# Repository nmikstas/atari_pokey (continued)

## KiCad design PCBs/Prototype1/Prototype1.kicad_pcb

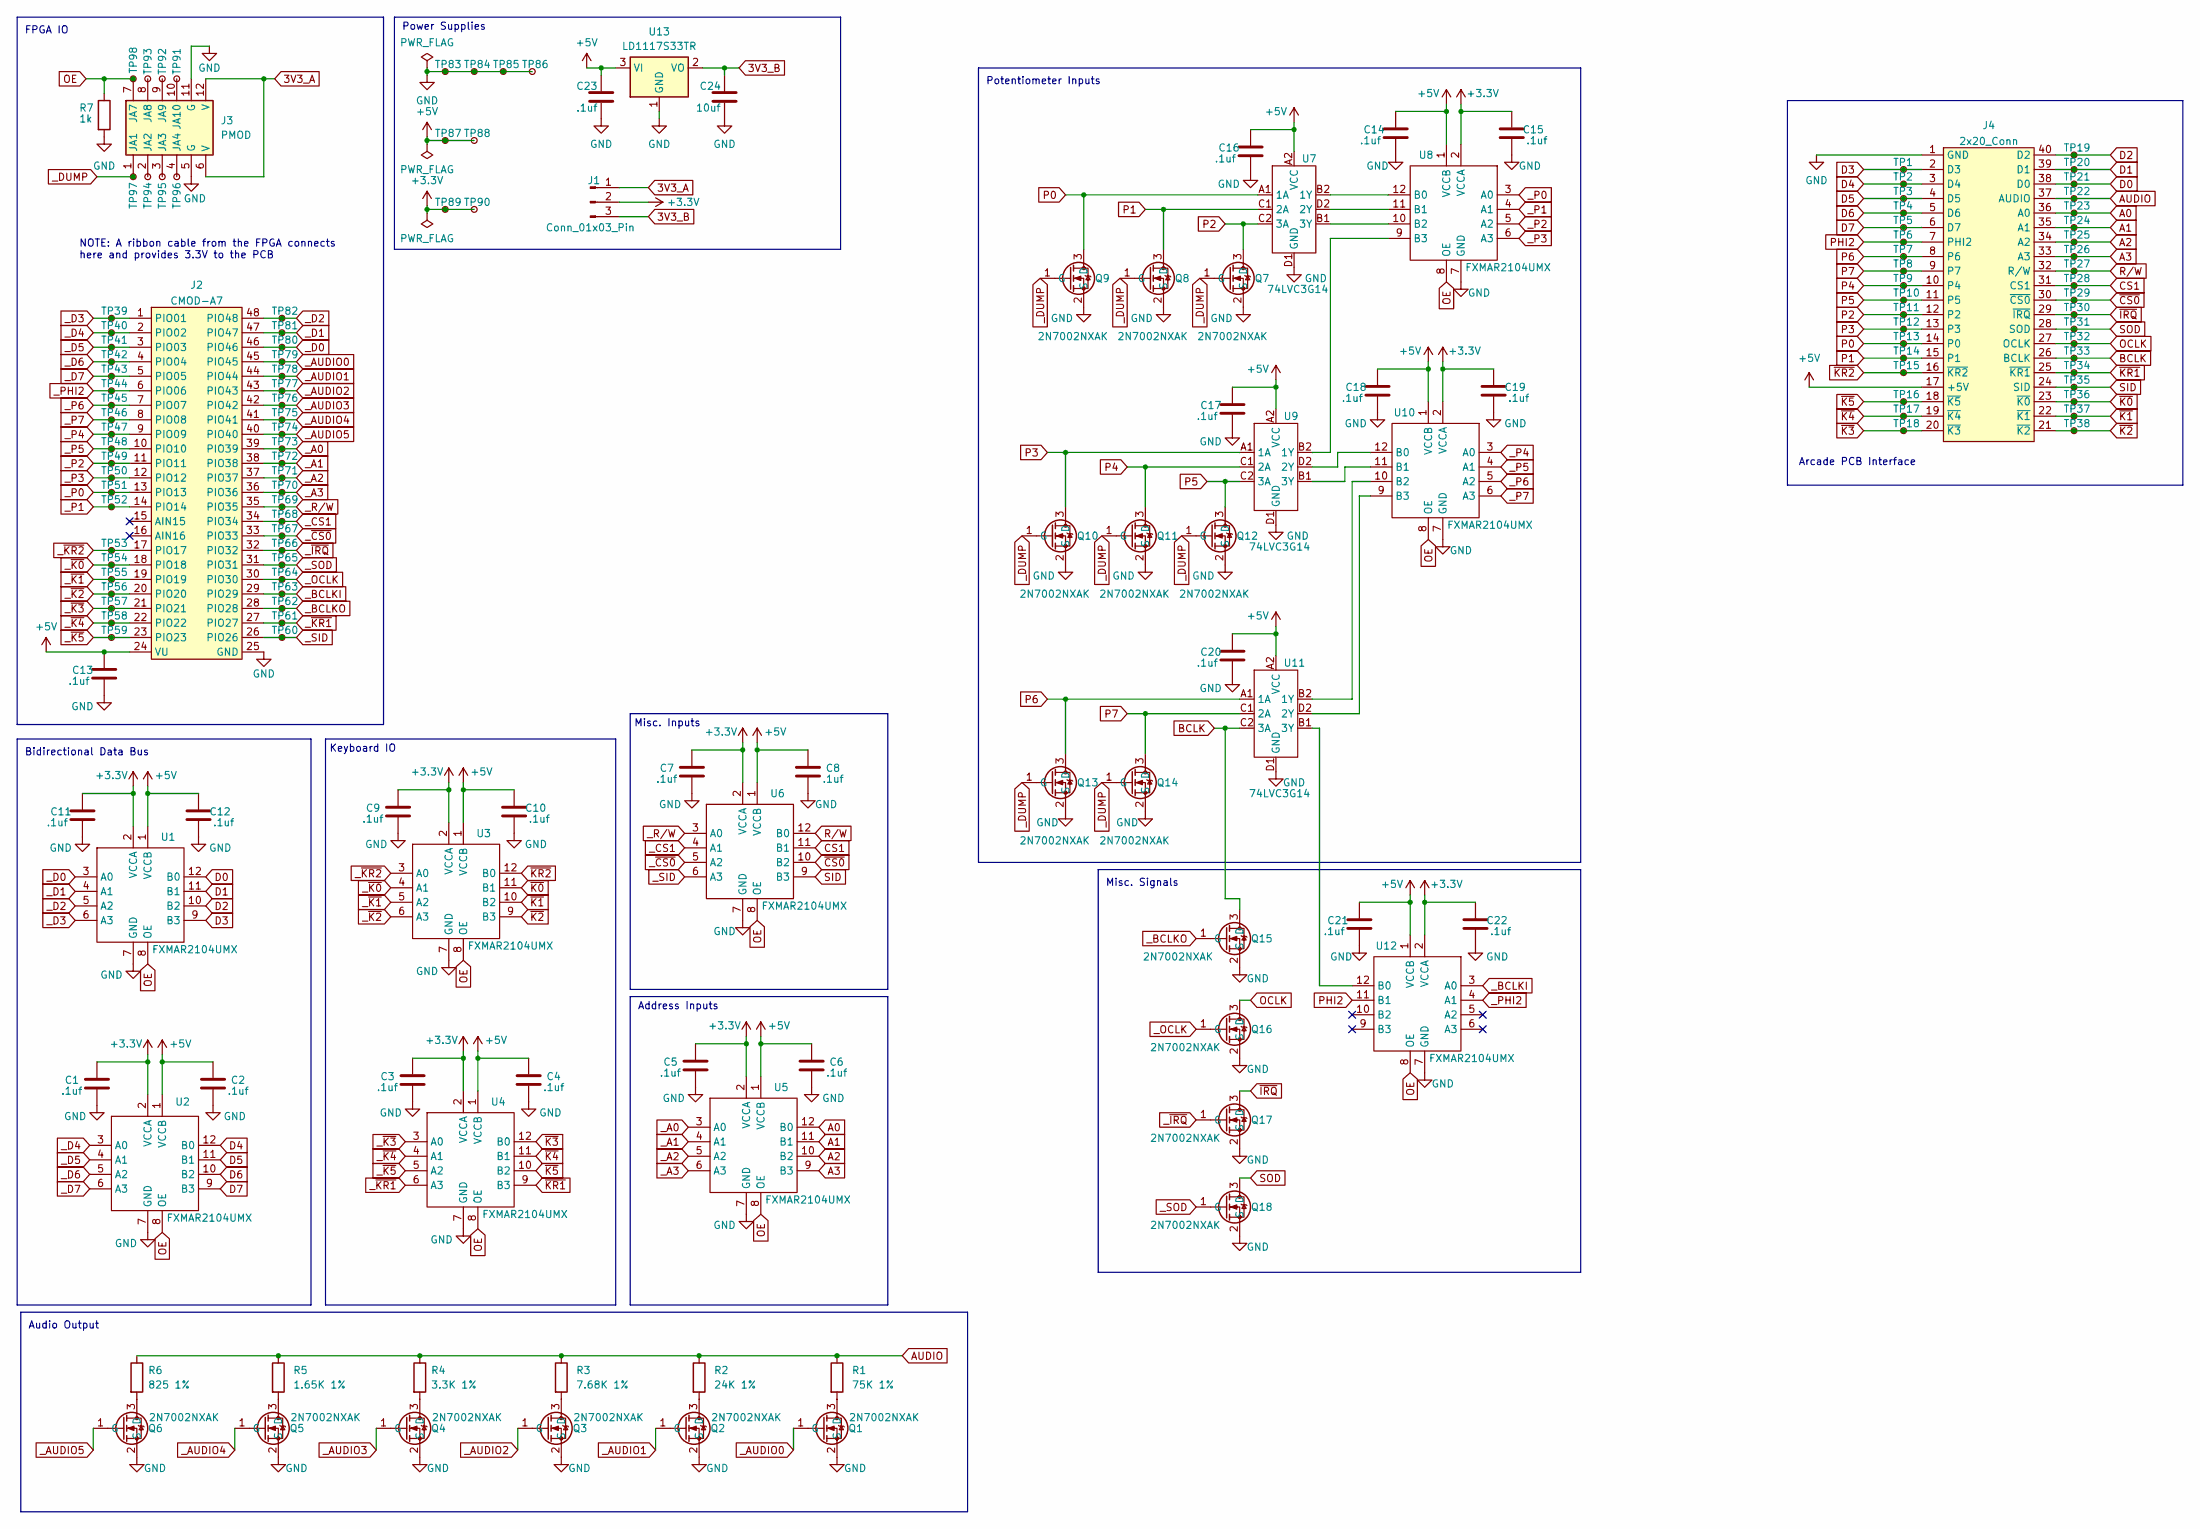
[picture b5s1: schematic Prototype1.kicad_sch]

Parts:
C1, C2, C3, C4, C5, C6, C7, C8, C9, C10, C11, C12, C13, C14, C15, C16, C17, C18, C19, C20, C21, C22, C23: .1uf; C_0402_1005Metric
C24: 10uf; C_0805_2012Metric
J1: Conn_01x03_Pin; PinSocket_1x03_P2.54mm_Vertical
J2: CMOD-A7; Con_2X24
J3: PMOD
J4: 2x20_Conn; Con_2X20
Q1, Q2, Q3, Q4, Q5, Q6, Q7, Q8, Q9, Q10, Q11, Q12, Q13, Q14, Q15, Q16, Q17, Q18: 2N7002NXAK; SOT-23-3
R1: 75K 1%; R_0402_1005Metric
R2: 24K 1%; R_0402_1005Metric
R3: 7.68K 1%; R_0402_1005Metric
R4: 3.3K 1%; R_0402_1005Metric
R5: 1.65K 1%; R_0402_1005Metric
R6: 825 1%; R_0402_1005Metric
R7: 1k; R_0402_1005Metric
TP1, TP2, TP3, TP4, TP5, TP6, TP7, TP8, TP9, TP10, TP11, TP12, TP13, TP14, TP15, TP16, TP17, TP18, TP19, TP20, TP21, TP22, TP23, TP24, TP25, TP26, TP27, TP28, TP29, TP30, TP31, TP32, TP33, TP34, TP35, TP36, TP37, TP38, TP39, TP40, TP41, TP42, TP43, TP44, TP45, TP46, TP47, TP48, TP49, TP50, TP51, TP52, TP53, TP54, TP55, TP56, TP57, TP58, TP59, TP60, TP61, TP62, TP63, TP64, TP65, TP66, TP67, TP68, TP69, TP70, TP71, TP72, TP73, TP74, TP75, TP76, TP77, TP78, TP79, TP80, TP81, TP82, TP83, TP84, TP85, TP86, TP87, TP88, TP89, TP90, TP91, TP92, TP93, TP94, TP95, TP96, TP97, TP98: TP
U1, U2, U3, U4, U5, U6, U8, U10, U12: FXMAR2104UMX; ULTRATHIN_MLP_12L_ONS-L
U7, U9, U11: 74LVC3G14; YZP8
U13: LD1117S33TR; Reg

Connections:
3V3_A: J1.1, J3.6 (V), J3.12 (V)
3V3_B: C24.1, J1.3, U13.2 (VO)
+3.3V: C1.1, C3.1, C5.1, C7.1, C9.1, C11.1, C15.1, C19.1, C22.1, J1.2, TP89.1, TP90.1, U1.2 (VCCA), U2.2 (VCCA), U3.2 (VCCA), U4.2 (VCCA), U5.2 (VCCA), U6.2 (VCCA), U8.2 (VCCA), U10.2 (VCCA), U12.2 (VCCA)
+5V: C2.1, C4.1, C6.1, C8.1, C10.1, C12.1, C13.1, C14.1, C16.1, C17.1, C18.1, C20.1, C21.1, C23.1, J2.24 (VU), J4.17 (+5V), TP87.1, TP88.1, U1.1 (VCCB), U2.1 (VCCB), U3.1 (VCCB), U4.1 (VCCB), U5.1 (VCCB), U6.1 (VCCB), U7.A2 (VCC), U8.1 (VCCB), U9.A2 (VCC), U10.1 (VCCB), U11.A2 (VCC), U12.1 (VCCB), U13.3 (VI)
A0: J4.36 (A0), TP23.1, U5.12 (B0)
A1: J4.35 (A1), TP24.1, U5.11 (B1)
A2: J4.34 (A2), TP25.1, U5.10 (B2)
A3: J4.33 (A3), TP26.1, U5.9 (B3)
AUDIO: J4.37 (AUDIO), R1.1, R2.1, R3.1, R4.1, R5.1, R6.1, TP22.1
BCLK: J4.26 (BCLK), Q15.3 (D), TP33.1, U11.C2 (3A)
CS1: J4.31 (CS1), TP28.1, U6.11 (B1)
D0: J4.38 (D0), TP21.1, U1.12 (B0)
D1: J4.39 (D1), TP20.1, U1.11 (B1)
D2: J4.40 (D2), TP19.1, U1.10 (B2)
D3: J4.2 (D3), TP1.1, U1.9 (B3)
D4: J4.3 (D4), TP2.1, U2.12 (B0)
D5: J4.4 (D5), TP3.1, U2.11 (B1)
D6: J4.5 (D6), TP4.1, U2.10 (B2)
D7: J4.6 (D7), TP5.1, U2.9 (B3)
GND: C1.2, C2.2, C3.2, C4.2, C5.2, C6.2, C7.2, C8.2, C9.2, C10.2, C11.2, C12.2, C13.2, C14.2, C15.2, C16.2, C17.2, C18.2, C19.2, C20.2, C21.2, C22.2, C23.2, C24.2, J2.25 (GND), J3.5 (G), J3.11 (G), J4.1 (GND), Q1.2 (S), Q2.2 (S), Q3.2 (S), Q4.2 (S), Q5.2 (S), Q6.2 (S), Q7.2 (S), Q8.2 (S), Q9.2 (S), Q10.2 (S), Q11.2 (S), Q12.2 (S), Q13.2 (S), Q14.2 (S), Q15.2 (S), Q16.2 (S), Q17.2 (S), Q18.2 (S), R7.2, TP83.1, TP84.1, TP85.1, TP86.1, U1.7 (GND), U2.7 (GND), U3.7 (GND), U4.7 (GND), U5.7 (GND), U6.7 (GND), U7.D1 (GND), U8.7 (GND), U9.D1 (GND), U10.7 (GND), U11.D1 (GND), U12.7 (GND), U13.1 (GND)
unnamed: J3.2 (JA2), TP94.1
unnamed: J3.3 (JA3), TP95.1
unnamed: J3.4 (JA4), TP96.1
unnamed: J3.8 (JA8), TP93.1
unnamed: J3.9 (JA9), TP92.1
unnamed: J3.10 (JA10), TP91.1
unnamed: Q1.3 (D), R1.2
unnamed: Q2.3 (D), R2.2
unnamed: Q3.3 (D), R3.2
unnamed: Q4.3 (D), R4.2
unnamed: Q5.3 (D), R5.2
unnamed: Q6.3 (D), R6.2
unnamed: U7.B2 (1Y), U8.12 (B0)
unnamed: U7.D2 (2Y), U8.11 (B1)
unnamed: U7.B1 (3Y), U8.10 (B2)
unnamed: U8.9 (B3), U9.B2 (1Y)
unnamed: U9.D2 (2Y), U10.12 (B0)
unnamed: U9.B1 (3Y), U10.11 (B1)
unnamed: U10.10 (B2), U11.B2 (1Y)
unnamed: U10.9 (B3), U11.D2 (2Y)
unnamed: U11.B1 (3Y), U12.12 (B0)
OCLK: J4.27 (OCLK), Q16.3 (D), TP32.1
OE: J3.7 (JA7), R7.1, TP98.1, U1.8 (OE), U2.8 (OE), U3.8 (OE), U4.8 (OE), U5.8 (OE), U6.8 (OE), U8.8 (OE), U10.8 (OE), U12.8 (OE)
P0: J4.14 (P0), Q9.3 (D), TP13.1, U7.A1 (1A)
P1: J4.15 (P1), Q8.3 (D), TP14.1, U7.C1 (2A)
P2: J4.12 (P2), Q7.3 (D), TP11.1, U7.C2 (3A)
P3: J4.13 (P3), Q10.3 (D), TP12.1, U9.A1 (1A)
P4: J4.10 (P4), Q11.3 (D), TP9.1, U9.C1 (2A)
P5: J4.11 (P5), Q12.3 (D), TP10.1, U9.C2 (3A)
P6: J4.8 (P6), Q13.3 (D), TP7.1, U11.A1 (1A)
P7: J4.9 (P7), Q14.3 (D), TP8.1, U11.C1 (2A)
PHI2: J4.7 (PHI2), TP6.1, U12.11 (B1)
R/W: J4.32 (R/W), TP27.1, U6.12 (B0)
SID: J4.24 (SID), TP35.1, U6.9 (B3)
SOD: J4.28 (SOD), Q18.3 (D), TP31.1
_A0: J2.39 (PIO39), TP73.1, U5.3 (A0)
_A1: J2.38 (PIO38), TP72.1, U5.4 (A1)
_A2: J2.37 (PIO37), TP71.1, U5.5 (A2)
_A3: J2.36 (PIO36), TP70.1, U5.6 (A3)
_AUDIO0: J2.45 (PIO45), Q1.1 (G), TP79.1
_AUDIO1: J2.44 (PIO44), Q2.1 (G), TP78.1
_AUDIO2: J2.43 (PIO43), Q3.1 (G), TP77.1
_AUDIO3: J2.42 (PIO42), Q4.1 (G), TP76.1
_AUDIO4: J2.41 (PIO41), Q5.1 (G), TP75.1
_AUDIO5: J2.40 (PIO40), Q6.1 (G), TP74.1
_BCLKI: J2.29 (PIO29), TP63.1, U12.3 (A0)
_BCLKO: J2.28 (PIO28), Q15.1 (G), TP62.1
_CS1: J2.34 (PIO34), TP68.1, U6.4 (A1)
_D0: J2.46 (PIO46), TP80.1, U1.3 (A0)
_D1: J2.47 (PIO47), TP81.1, U1.4 (A1)
_D2: J2.48 (PIO48), TP82.1, U1.5 (A2)
_D3: J2.1 (PIO01), TP39.1, U1.6 (A3)
_D4: J2.2 (PIO02), TP40.1, U2.3 (A0)
_D5: J2.3 (PIO03), TP41.1, U2.4 (A1)
_D6: J2.4 (PIO04), TP42.1, U2.5 (A2)
_D7: J2.5 (PIO05), TP43.1, U2.6 (A3)
_DUMP: J3.1 (JA1), Q7.1 (G), Q8.1 (G), Q9.1 (G), Q10.1 (G), Q11.1 (G), Q12.1 (G), Q13.1 (G), Q14.1 (G), TP97.1
_OCLK: J2.30 (PIO30), Q16.1 (G), TP64.1
_P0: J2.13 (PIO13), TP51.1, U8.3 (A0)
_P1: J2.14 (PIO14), TP52.1, U8.4 (A1)
_P2: J2.11 (PIO11), TP49.1, U8.5 (A2)
_P3: J2.12 (PIO12), TP50.1, U8.6 (A3)
_P4: J2.9 (PIO09), TP47.1, U10.3 (A0)
_P5: J2.10 (PIO10), TP48.1, U10.4 (A1)
_P6: J2.7 (PIO07), TP45.1, U10.5 (A2)
_P7: J2.8 (PIO08), TP46.1, U10.6 (A3)
_PHI2: J2.6 (PIO06), TP44.1, U12.4 (A1)
_R/W: J2.35 (PIO35), TP69.1, U6.3 (A0)
_SID: J2.26 (PIO26), TP60.1, U6.6 (A3)
_SOD: J2.31 (PIO31), Q18.1 (G), TP65.1
_~CS0: J2.33 (PIO33), TP67.1, U6.5 (A2)
_~IRQ: J2.32 (PIO32), Q17.1 (G), TP66.1
_~K0: J2.18 (PIO18), TP54.1, U3.4 (A1)
_~K1: J2.19 (PIO19), TP55.1, U3.5 (A2)
_~K2: J2.20 (PIO20), TP56.1, U3.6 (A3)
_~K3: J2.21 (PIO21), TP57.1, U4.3 (A0)
_~K4: J2.22 (PIO22), TP58.1, U4.4 (A1)
_~K5: J2.23 (PIO23), TP59.1, U4.5 (A2)
_~KR1: J2.27 (PIO27), TP61.1, U4.6 (A3)
_~KR2: J2.17 (PIO17), TP53.1, U3.3 (A0)
~CS0: J4.30 (~CS0), TP29.1, U6.10 (B2)
~IRQ: J4.29 (~IRQ), Q17.3 (D), TP30.1
~K0: J4.23 (~K0), TP36.1, U3.11 (B1)
~K1: J4.22 (~K1), TP37.1, U3.10 (B2)
~K2: J4.21 (~K2), TP38.1, U3.9 (B3)
~K3: J4.20 (~K3), TP18.1, U4.12 (B0)
~K4: J4.19 (~K4), TP17.1, U4.11 (B1)
~K5: J4.18 (~K5), TP16.1, U4.10 (B2)
~KR1: J4.25 (~KR1), TP34.1, U4.9 (B3)
~KR2: J4.16 (~KR2), TP15.1, U3.12 (B0)

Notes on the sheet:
Arcade PCB Interface
Bidirectional Data Bus
Address Inputs
Misc. Signals
Potentiometer Inputs
Misc. Inputs
Keyboard IO
FPGA IO
NOTE: A ribbon cable from the FPGA connects here and provides 3.3V to the PCB
Audio Output
Power Supplies

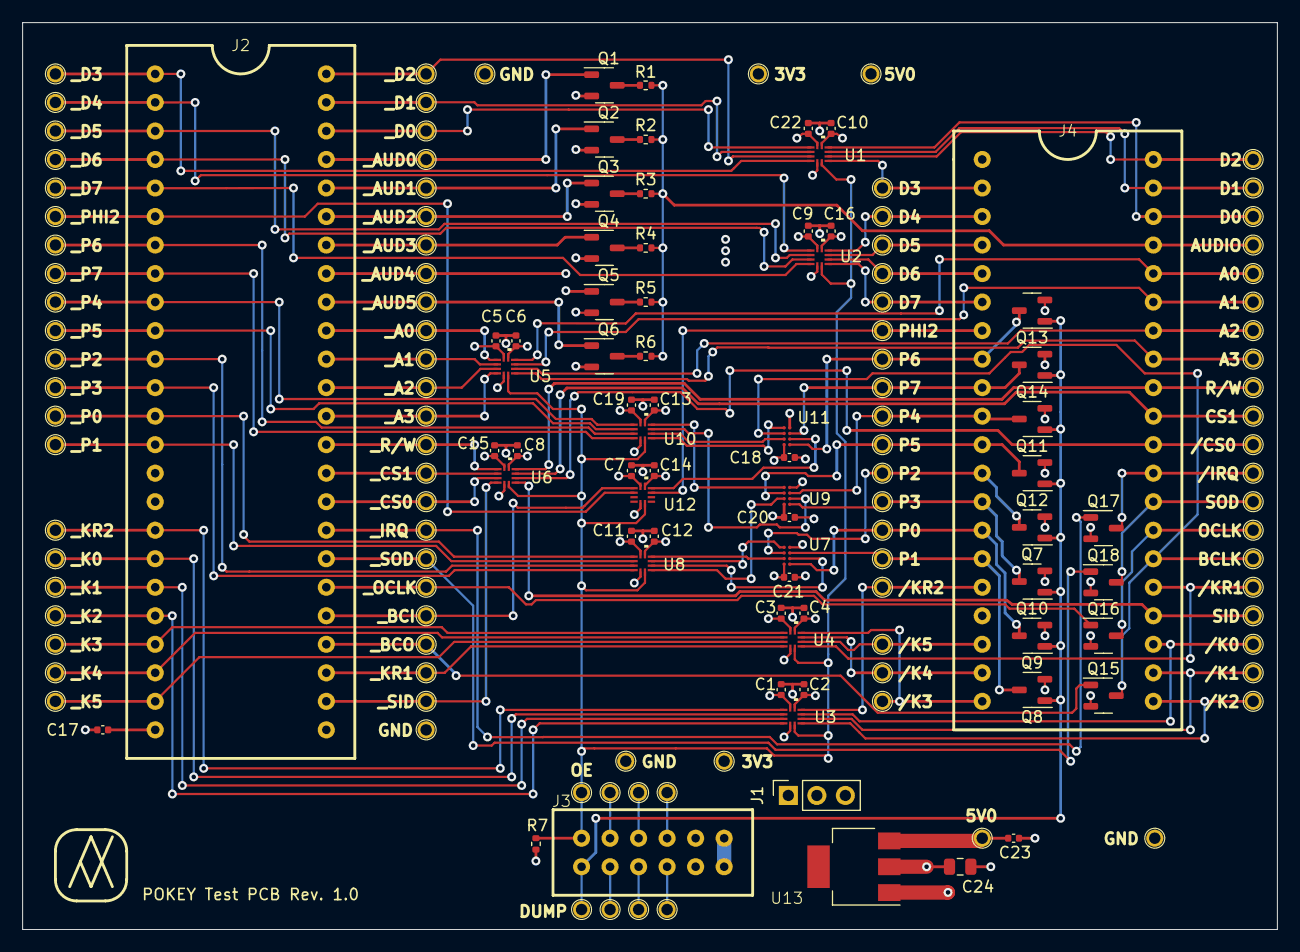
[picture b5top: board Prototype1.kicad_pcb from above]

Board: 4 copper layers, 111.8 x 80.8 mm, 164 parts (0 on the bottom side), 110 nets.

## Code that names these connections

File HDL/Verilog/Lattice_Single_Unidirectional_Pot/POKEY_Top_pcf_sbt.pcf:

# ##############################################################################

# iCEcube PCF

# Version:            2020.12.27943

# File Generated:     Dec 5 2024 22:41:23

# Family & Device:    iCE40HX8K

# Package:            CB132

# ##############################################################################

###IOSet List 53
set_io d[7] K4
set_io irq C7
set_io k[1] H12
set_io leds[3] K14
set_io bclko C11
set_io p[2] A7
set_io d[1] K3
set_io en F4
set_io audio[5] D1
set_io k[4] H11
set_io leds[4] L12
set_io p[4] D5
set_io d[3] J1
set_io dev_clk P7
set_io k[2] J12
set_io leds[6] M12
set_io p[6] C4
set_io a[1] H4
set_io audio[2] G3
set_io d[5] J3
set_io k[3] G11
set_io kr[1] D14
set_io leds[1] K11
set_io p[1] A12
set_io sod D6
set_io a[2] F3
set_io audio[1] H3
set_io bclki B14
set_io d[4] M1
set_io k[0] C14
set_io kr[2] D12
set_io leds[0] J11
set_io oclk D7
set_io p[0] C12
set_io rw C1
set_io sid A2
set_io a[3] B1
set_io audio[0] G1
set_io p[3] C6
set_io d[6] L1
set_io leds[2] K12
set_io dump A11
set_io leds[5] L14
set_io p[5] A10
set_io d[0] P1
set_io audio[4] E1
set_io clk A6
set_io k[5] D11
set_io leds[7] N14
set_io p[7] A1
set_io a[0] G4
set_io audio[3] H1
set_io d[2] N1

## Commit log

2022-12-24 Added some images
2022-12-25 Finished clock gen core and restructured project folders
2023-01-03 Worked on frequency control registers and simulations
2023-01-04 Completed frequency controller simulations and added poly core images
2023-01-05 Performed fequency control register simulations
2023-01-07 Worked on poly core simulations
2023-01-07 Added MAME random number sequences in a text file
2023-01-07 Added rng image
2023-01-07 Changed init signal on the 4-bit poly so it is asynchronous
2023-01-08 Updated poly_core
2023-01-13 Finished the IO core
2023-01-13 Rearranged the structure of the repository
2023-01-14 Added documents for the POT core
2023-01-14 Created simulation for POT core counter
2023-01-16 Finished the POT core code and simulations
2023-01-17 Added pot core simulation images
2023-01-21 Made images for 2 registers and the 3 PLA circuits
2023-01-21 Added control registers and PLA source code
2023-01-22 Added keyboard state machine images
2023-01-22 Worked on the top level
2023-01-25 worked on keyboard scanner
2023-01-28 Made images of keyboard scanner logic
2023-01-28 Started writing HDL for the keyboard scanner
2023-01-29 Built and simulated individual components of the keyboard scanner core
2023-01-29 Built the KEY core and began writing test bench
2023-01-29 Cleaned up repository and finished KEY core simulations
2023-01-29 Modified gitignore file
2023-01-29 Finished the KEY core HDL and simulations!
2023-01-31 Started working on IRQ core and SKSTAT register
2023-02-02 Worked on the IRQ core and SKSTAT register
2023-02-03 Finshed IRQ core and SKSTAT reg
2023-02-05 Completed the integration of the IRQ core, KEY core and SKSTAT register into the top level
2023-02-06 Laid out audio frequency control circuit images
2023-02-08 Began work on the audio frequency control block
2023-02-09 Finished the audio frequency control module
2023-02-12 Added serial out state machine graphics
2023-02-13 Added serial out shift register
2023-02-18 Finished the serial clock generator and its simulations
2023-02-19 Completed serial transmit hardware
2023-02-25 Added SERIN images
2023-02-27 Completed the SERIN hardware module
2023-03-05 Updated HDL
2023-03-07 Finished all cores and added them to the top level
2023-03-08 Fixed errors in the serial in IRQ signal and timer 4 signal
2023-03-11 Finished POKEY simulations
2024-08-17 Began conversion to verilog
2024-08-24 Designed prototyping PCB
2024-09-08 Made prototype board and completed more verilog conversions
2024-09-08 Completed KEY core optimizations
2024-09-16 Completed frequency control
2024-09-20 Worked on serial core
2024-09-22 Finished serial core and IRQ core
2024-09-29 Finished verilog POKEY code
2024-10-05 Worked on FPGA simulation
2024-10-20 Added new prototype PCBs
2024-11-11 Rearranged the repository
2024-12-10 Added several new test boards
